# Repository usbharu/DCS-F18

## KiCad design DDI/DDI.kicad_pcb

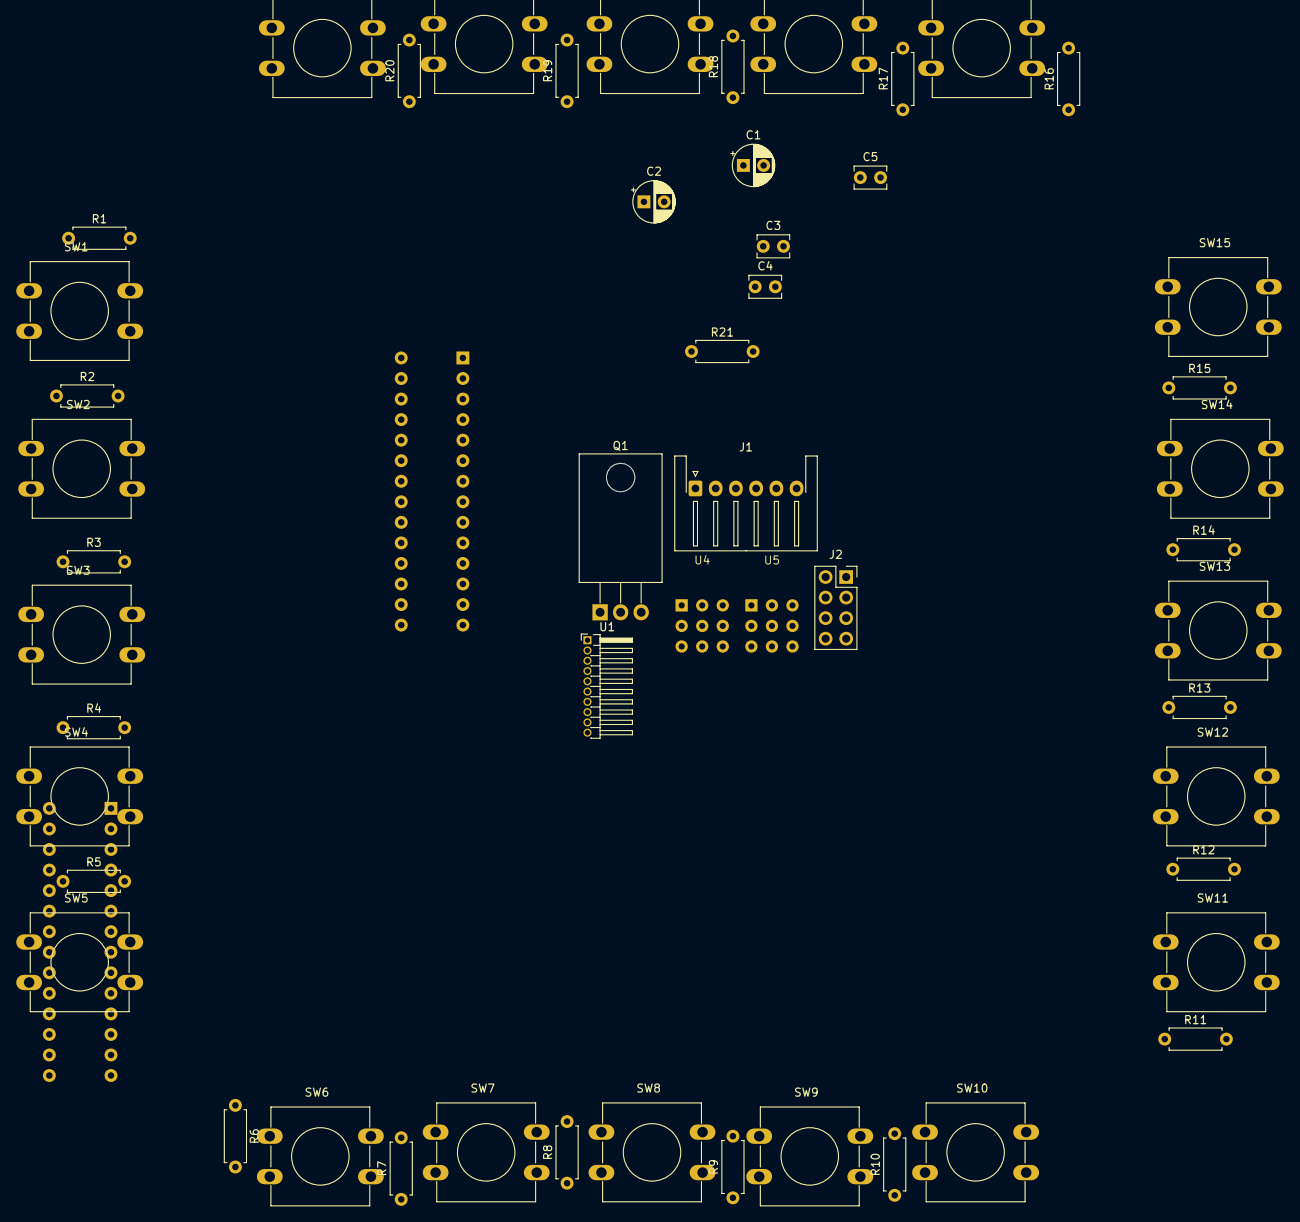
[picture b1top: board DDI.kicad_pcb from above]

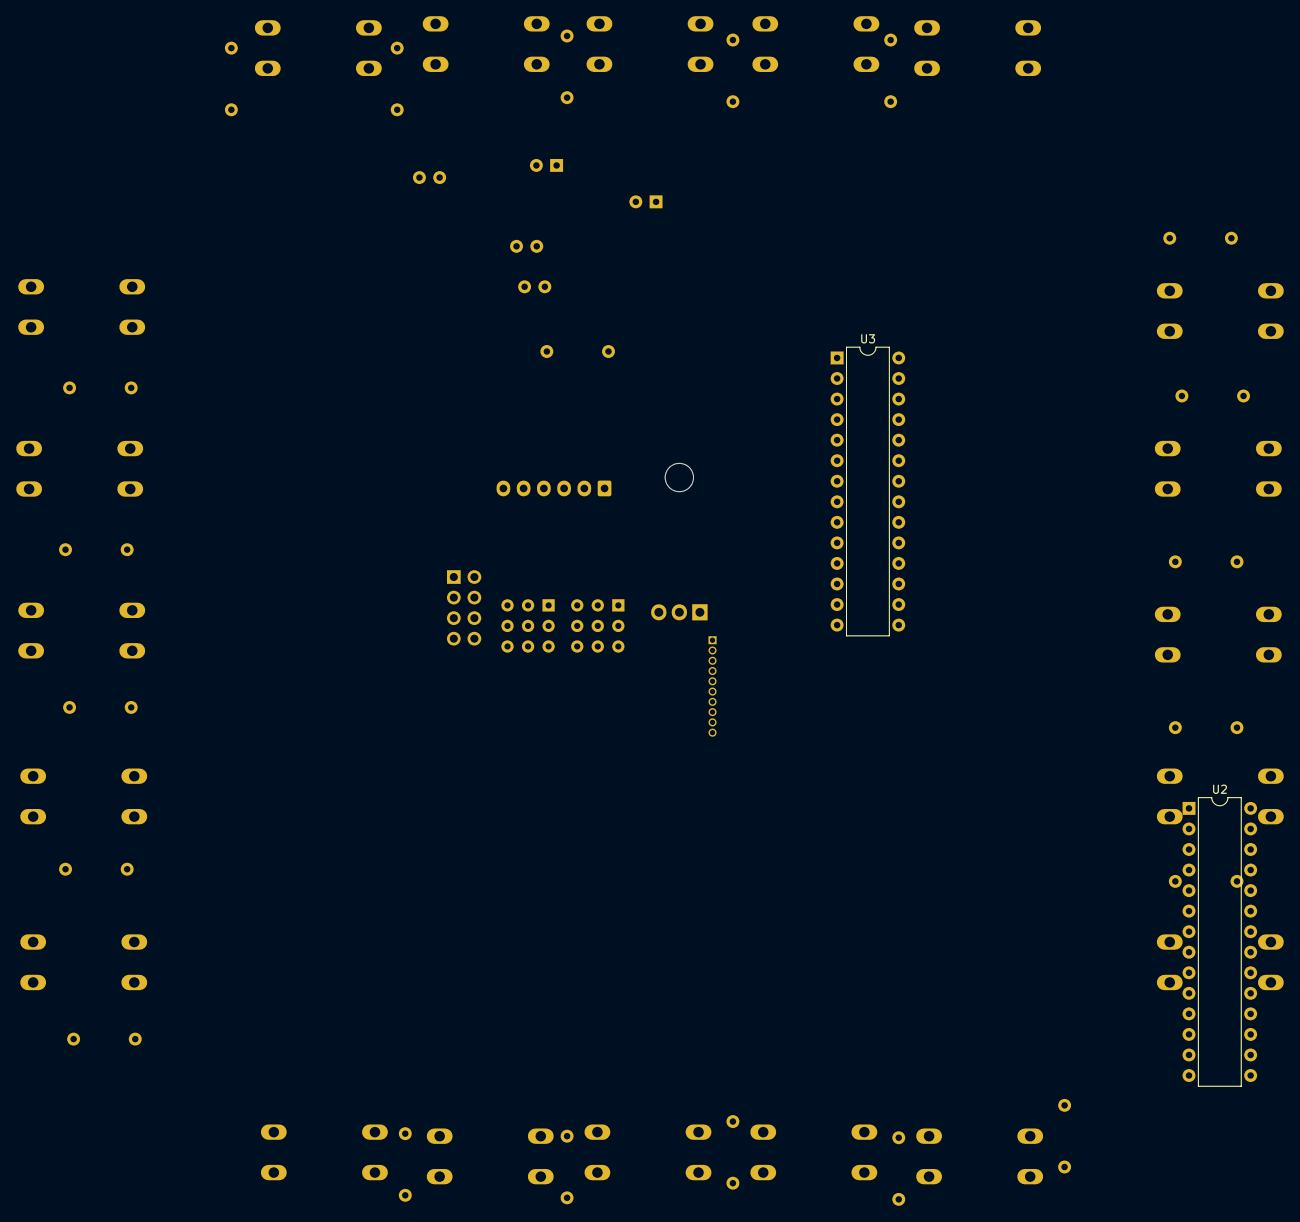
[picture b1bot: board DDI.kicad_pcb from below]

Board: 2 copper layers, 54 parts (2 on the bottom side), 33 nets, no tracks yet.

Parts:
C1, C2: C_Polarized; CP_Radial_D5.0mm_P2.50mm
C3, C4, C5: 0.1uF; C_Disc_D3.8mm_W2.6mm_P2.50mm
J1: Conn_01x06_Socket; JST_XH_S6B-XH-A-1_1x06_P2.50mm_Horizontal
J2: Conn_02x04_Top_Bottom; PinSocket_2x04_P2.54mm_Vertical
Q1: Q_NMOS_GDS; TO-220-3_Horizontal_TabDown
R1, R2, R3, R4, R5, R6, R7, R8, R9, R10, R11, R12, R13, R14, R15, R16, R17, R18, R19, R20, R21: R; R_Axial_DIN0207_L6.3mm_D2.5mm_P7.62mm_Horizontal
SW1, SW2, SW3, SW4, SW5, SW6, SW7, SW8, SW9, SW10, SW11, SW12, SW13, SW14, SW15, SW16, SW17, SW18, SW19, SW20: SW_Push; SW_PUSH-12mm
U1: ADS1015IDGS; PinHeader_1x10_P1.27mm_Horizontal
U2, U3: MCP23017_SP; DIP-28_W7.62mm
U4, U5: Connector_PinSocket_2.54mmPinSocket_3x03_P2.54mm_Vertical

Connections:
+5V: C2.1, J1.2, R21.1
/DDI-1: R1.1, SW1.1, U2.1 (GPB0)
/DDI-2: R2.1, SW2.1, U2.2 (GPB1)
/DDI-3: R3.1, SW3.1, U2.3 (GPB2)
/DDI-4: R4.1, SW4.1, U2.4 (GPB3)
/DDI-5: R5.1, SW5.1, U2.5 (GPB4)
/DDI-6: R6.1, SW6.1, U2.6 (GPB5)
/DDI-7: R7.1, SW7.1, U2.7 (GPB6)
/DDI-8: R8.1, SW8.1, U2.8 (GPB7)
/DDI-9: R9.1, SW9.1, U2.21 (GPA0)
/DDI-10: R10.1, SW10.1, U2.22 (GPA1)
/DDI-11: R11.1, SW11.1, U2.23 (GPA2)
/DDI-12: R12.1, SW12.1, U2.24 (GPA3)
/DDI-13: R13.1, SW13.1, U2.25 (GPA4)
/DDI-14: R14.1, SW14.1, U2.26 (GPA5)
/DDI-15: R15.1, SW15.1, U2.27 (GPA6)
/DDI-16: R16.1, SW16.1, U2.28 (GPA7)
/DDI-17: R17.1, SW17.1, U3.1 (GPB0)
/DDI-18: R18.1, SW18.1, U3.2 (GPB1)
/DDI-19: R19.1, SW19.1, U3.3 (GPB2)
/DDI-20: R20.1, SW20.1, U3.4 (GPB3)
/DDI-LED-1: Q1.1 (G), U3.21 (GPA0)
DDI+3.3V: C1.1, C3.1, C4.1, C5.1, J1.1, J2.7, SW1.2, SW2.2, SW3.2, SW4.2, SW5.2, SW6.2, SW7.2, SW8.2, SW9.2, SW10.2, SW11.2, SW12.2, SW13.2, SW14.2, SW15.2, SW16.2, SW17.2, SW18.2, SW19.2, SW20.2, U1.8 (VDD), U2.9 (VDD), U2.18 (~RESET), U3.9 (VDD), U3.18 (~RESET), U4.1, U4.2, U4.3, U5.1, U5.2, U5.3
DDI-GND: C1.2, C2.2, C3.2, C4.2, C5.2, J1.6, J2.8, Q1.3 (S), R1.2, R2.2, R3.2, R4.2, R5.2, R6.2, R7.2, R8.2, R9.2, R10.2, R11.2, R12.2, R13.2, R14.2, R15.2, R16.2, R17.2, R18.2, R19.2, R20.2, U1.3 (GND), U2.10 (VSS), U3.10 (VSS), U4.7, U4.8, U4.9, U5.7, U5.8, U5.9
unnamed: J1.3, J2.6, U1.9 (SDA), U2.13 (SDA), U3.13 (SDA)
unnamed: J1.4, J2.5, U1.10 (SCL), U2.12 (SCK), U3.12 (SCK)
unnamed: J2.1, J2.2, J2.3, J2.4, U1.1 (ADDR)
unnamed: U2.15 (A0), U4.6
unnamed: U2.16 (A1), U4.5
unnamed: U2.17 (A2), U4.4
unnamed: U3.15 (A0), U5.6
unnamed: U3.16 (A1), U5.5
unnamed: U3.17 (A2), U5.4

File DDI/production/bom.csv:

Designator,Footprint,Quantity,Value,LCSC Part #
"C1, C2",CP_Radial_D5.0mm_P2.50mm,2,C_Polarized,
"C3, C4, C5",C_Disc_D3.8mm_W2.6mm_P2.50mm,3,0.1uF,
J1,JST_XH_S6B-XH-A-1_1x06_P2.50mm_Horizontal,1,Conn_01x06_Socket,
J2,PinSocket_2x04_P2.54mm_Vertical,1,Conn_02x04_Top_Bottom,
Q1,TO-220-3_Horizontal_TabDown,1,Q_NMOS_GDS,
"R1, R10, R11, R12, R13, R14, R15, R16, R17, R18, R19, R2, R20, R21, R3, R4, R5, R6, R7, R8, R9",R_Axial_DIN0207_L6.3mm_D2.5mm_P7.62mm_Horizontal,21,R,
"SW1, SW10, SW11, SW12, SW13, SW14, SW15, SW16, SW17, SW18, SW19, SW2, SW20, SW3, SW4, SW5, SW6, SW7, SW8, SW9",SW_PUSH-12mm,20,SW_Push,
U1,PinHeader_1x10_P1.27mm_Horizontal,1,ADS1015IDGS,
"U2, U3",DIP-28_W7.62mm,2,MCP23017_SP,
"U4, U5",Connector_PinSocket_2.54mmPinSocket_3x03_P2.54mm_Vertical,2,~,

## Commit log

2024-10-28 feat: thread::sleepの代わりにtime::sleepを使用するように
2024-10-28 DCS-BIOS-Viewerを使えるように
2024-10-30 moduleやcategoriesやidが一つしかなかったときに選択できなかった問題を修正
2024-10-30 削除できるように
2024-10-30 エラーを表示するように
2024-10-30 update cargolock
2024-10-31 enumで出力できるように
2024-10-31 文字列型に対応
2024-10-31 クライアントでも文字列に対応
2024-11-01 取得できないデータがあることがわかったので開発中止
2024-11-01 一旦全部ふっとばした
2024-11-02 多分ちゃんとプロトコル解析できるようになった
2024-11-02 不要なuseを削除
2024-11-03 全てのデータを読み取れるように
2024-11-04 fix lint
2024-11-05 モジュールをソートして表示し、タイムアウトのエラーを表示しないように
2024-11-05 フィルターを作成できるように
2024-11-06 web ui 作りかけ
2024-11-06 デザインやった
2024-12-01 DDIを変更
2024-12-09 dcs-bios-rsを動かすように
2024-12-10 metricsの追加削除ができるように
2024-12-10 DCSでちゃんと動くように!!!
2024-12-11 embassyでi2cをembeddex_halといい感じに使う方法がわかった
2024-12-12 マルチプロジェクトな感じに wip
2024-12-12 コンパイルに失敗する問題を修正
2024-12-12 libに
2024-12-12 vscodeの設定を同期するように
2024-12-12 style: fix style
2024-12-12 workspace.dependenciesを活用するように
2024-12-12 ワークスペースの依存関係にddiを追加
2024-12-12 refactor
2024-12-12 ddiの抽象化を進めた
2024-12-13 使うライブラリを変えた ピンを読めるようにした
2024-12-13 select等を読めるように
2024-12-13 必要ないuseを消す
